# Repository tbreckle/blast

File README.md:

<div align="center">

### Button Logic & Arcade Simulation Terminal

**An open-source arcade control panel: 16 buttons, 11 dimmable LEDs, an OLED menu, and a desktop app to configure all of it.**

[**Download**](https://github.com/tbreckle/blast/releases) ·
[Features](#-features) ·
[Quick start](#-quick-start) ·
[BLAST protocol](#-light-it-up-from-your-games) ·
[Building](#-building-from-source) ·
[Contributing](#-contributing)

</div>

---

## 🕹️ What is this?

B.L.A.S.T. is the button box that sits next to your lightgun or arcade cabinet. It presents itself to the PC as a plain **USB keyboard**, so every game and emulator understands it without drivers. Each game gets its own **profile** of key bindings, which you pick on the built-in **OLED** or let your frontend switch automatically. The **button LEDs** can be driven live by the game (blink the coin button, breathe the start button, flash on a hit) over a simple text protocol.

It's a full stack in one repo:

| | Component | Stack |
|---|---|---|
| 🧠 | [**Firmware**](firmware/) | C++ / Arduino on a Raspberry Pi Pico (RP2040 / RP2350) |
| 🖥️ | [**Config app**](app/) | Rust + [Slint](https://slint.dev), native on Linux, Windows and macOS |
| 🔌 | [**PCB**](pcb/) | KiCad schematic, layout and production files |

## ✨ Features

<table>
<tr>
<td width="50%" valign="top">

#### 🎮 Controller
- **16 inputs**: Start, Coin, Action A and Action B for two players, Pause / Save / Load, and a 5-way navigation pad
- **Plug and play**: USB HID keyboard, no drivers needed
- **Key combos**: letters, digits, Space, Enter, F1–F24, with Ctrl / Alt / Shift
- **Interrupt-driven debouncing** with a polling fallback

</td>
<td width="50%" valign="top">

#### 💡 Lighting
- **11 LED buttons** on a 12-channel TLC59711 PWM driver with gamma correction
- **Modes**: off, on, blink, breathe and flash sequences
- **Game-driven**: games and tools set the LEDs live over the [BLAST protocol](firmware/BLAST_PROTOCOL.md)
- **RGB status LED** that shows boot, config and run state

</td>
</tr>
<tr>
<td width="50%" valign="top">

#### 📟 On-device
- **128×64 OLED** menu to browse and pick profiles
- **Up to 50 profiles** stored in flash
- **Automatic profile switching** by game name, for example from MAMEHooker
- **Service menu** for the service and test buttons

</td>
<td width="50%" valign="top">

#### 🖥️ Config app
- **Create, edit and delete profiles** and press a key to bind it
- **Sync status** that shows what's changed and what's saved on the device
- **Version check**: warns when app and firmware don't match
- **Light / Dark / System** themes

</td>
</tr>
</table>

## 🚀 Quick start

1. **Grab the latest release** from the [Releases page](https://github.com/tbreckle/blast/releases):

   | File | What it is |
   |---|---|
   | `blast-firmware-X.Y.Z.uf2` | Firmware for the controller |
   | `blast-app-X.Y.Z-linux-x86_64.tar.gz` | Config app for Linux |
   | `blast-app-X.Y.Z-windows-x86_64.zip` | Config app for Windows |
   | `blast-app-X.Y.Z-macos-universal.tar.gz` | Config app for macOS (Apple Silicon + Intel) |

2. **Flash the firmware**: hold **BOOTSEL** while plugging in the Pico and drop the `.uf2` onto the `RPI-RP2` drive that shows up.
3. **Run the app**, pick the **B.L.A.S.T.** port (it's preselected), and create your first profile.
4. **Play.** Choose the profile on the OLED, or let your frontend switch to it.

> [!TIP]
> Use the app and firmware from the **same release**. The app shows a warning in the status bar when they differ. Builds labeled `0.0.0+<commit>` are unofficial development builds.

## 🌈 Light it up from your games

Out of the box the serial port speaks the **BLAST protocol**: one line of plain ASCII per command, with no handshake and no replies. Anything that can write to a serial port can drive the LEDs.

```bash
stty -F /dev/ttyACM0 115200 raw -echo
printf 'B1\n'          > /dev/ttyACM0   # host started: all LEDs off
printf 'BLxtcrisis\n'  > /dev/ttyACM0   # load the profile for "tcrisis"
printf 'B4x0x2x200\n'  > /dev/ttyACM0   # both coin buttons blink fast
printf 'B3x1x4x1500\n' > /dev/ttyACM0   # P1 start breathes with a 3 s cycle
printf 'B5x2x3x5\n'    > /dev/ttyACM0   # P2 action A flashes 5 times
```

The full spec is in [`firmware/BLAST_PROTOCOL.md`](firmware/BLAST_PROTOCOL.md).

## 🧩 How it fits together

```mermaid
flowchart LR
    subgraph PC["🖥️ PC"]
        game["Game / emulator"]
        hook["LED output tool<br/>(e.g. MAMEHooker)"]
        app["B.L.A.S.T. config app"]
    end

    subgraph Pico["🧠 RP2040 / RP2350"]
        fw["Firmware"]
    end

    fw -- "USB HID keystrokes" --> game
    hook -- "BLAST text protocol<br/>(USB serial)" --> fw
    app <-- "SLIP binary protocol<br/>(same USB serial)" --> fw

    fw --- mcp["MCP23017<br/>16 buttons"]
    fw --- tlc["TLC59711<br/>12 LED channels"]
    fw --- oled["SSD1306<br/>128×64 OLED"]
```

One USB cable carries both the keyboard and the serial port. The serial port runs one of two protocols at a time: the **BLAST** text protocol for games (the default), or the binary **SLIP** protocol that the config app switches to while it's connected. The OLED shows which one is active (`B` or `S`).

<details>
<summary><b>🔩 Hardware bill of materials</b></summary>

| Part | Role | Interface |
|---|---|---|
| Raspberry Pi Pico (W) / RP2350 | Main MCU | – |
| MCP23017 | 16 button inputs, active-low with pull-ups | I²C `0x20` + interrupt |
| TLC59711 | 12-channel 16-bit PWM LED driver | Bit-banged SPI (GP6 / GP7) |
| SSD1306 | 128×64 OLED | I²C `0x3C` |
| RGB LED | Status indicator | GPIO |

KiCad sources and fabrication outputs (BOM, positions, netlist) are in [`pcb/blast/`](pcb/blast/).

</details>

<details>
<summary><b>🗂️ Repository layout</b></summary>

```
blast/
├── firmware/              # Arduino/C++ firmware for RP2040/RP2350
│   ├── firmware.ino       # Entry point, pin map, button + LED handling
│   ├── blast_protocol.*   # BLAST text protocol (host LED control)
│   ├── serializer.*       # SLIP binary protocol (config app)
│   ├── menu.*             # OLED menu state machine
│   ├── debounce_mcp.*     # MCP23017 debouncing
│   ├── storage.*          # Profile persistence and migrations
│   └── flash.sh           # One-shot flashing via picotool
├── app/                   # Rust/Slint configuration tool
│   ├── ui/app.slint       # UI definition
│   └── src/               # ui.rs, protocol.rs, slip.rs, types.rs, keymap.rs
├── pcb/blast/             # KiCad project + production files
├── scripts/               # version.sh, changelog.sh, test.sh
└── .github/workflows/     # CI, release-start, release-finish
```

</details>

## 🔧 Building from source

<details>
<summary><b>🖥️ Config app (Rust)</b></summary>

**Requirements:** Rust 1.92+ (needed by Slint 1.18). On Linux you also need `libudev-dev`, `libfontconfig-dev` and `pkg-config`.

```bash
cd app
cargo run --release     # build and launch
cargo test              # unit tests
cargo clippy            # lint (warnings fail CI)
cargo fmt --check       # formatting check
```

</details>

<details>
<summary><b>🧠 Firmware (Arduino-Pico)</b></summary>

**Requirements:**
- [Arduino-Pico](https://github.com/earlephilhower/arduino-pico) core by Earle F. Philhower, III, **version 6.1.1**<br/>
  Boards Manager URL: `https://github.com/earlephilhower/arduino-pico/releases/download/global/package_rp2040_index.json`
- Libraries:

  | Library | Version |
  |---|---|
  | Adafruit MCP23017 Arduino Library | 2.3.2 |
  | Adafruit SSD1306 | 2.5.16 |
  | Adafruit GFX Library | 1.12.4 |
  | Adafruit BusIO | 1.17.4 |

  Wire, SPI, EEPROM, Keyboard, HID_Keyboard and tusb-hid ship with the Arduino-Pico core.

**With `arduino-cli`** (from the repo root, same as CI):

```bash
arduino-cli compile \
  --fqbn "$(jq -r '.board + ":" + .configuration' .vscode/arduino.json)" \
  --output-dir _build firmware/firmware.ino

cd firmware && ./flash.sh        # finds the controller by VID/PID, reboots it into the bootloader, flashes it
```

> [!IMPORTANT]
> Always build with the full FQBN from `.vscode/arduino.json`. It selects the Pico W boot stage and the 128 KB filesystem layout. With another flash layout the stored profiles are lost.

**With the Arduino IDE:** open `firmware/firmware.ino`, select the Raspberry Pi Pico W board (Arduino-Pico core) with a 128 KB filesystem and the Pico SDK USB stack, then upload.

</details>

## 🤝 Contributing

Contributions are welcome! The project uses **GitFlow**: branch `feature/*` off `develop` and open a PR back to `develop`. CI builds the app on all three platforms, builds the firmware and runs the linters on every push.

- 📖 [GITFLOW.md](GITFLOW.md): branching, versioning and releases
- ⚙️ [.github/WORKFLOWS.md](.github/WORKFLOWS.md): the CI/CD pipelines
- 📝 [CHANGELOG.md](CHANGELOG.md): add your change under `## [Unreleased]`

## 📜 License

B.L.A.S.T. is released under the [MIT License](LICENSE).

### Made with Slint

<a href="https://slint.dev">
  <picture>
    <source media="(prefers-color-scheme: dark)" srcset="https://slint.dev/logo/MadeWithSlint-logo-dark.svg">
    
  </picture>
</a>

The configuration tool's user interface is built with [Slint](https://slint.dev), used under the [Slint Royalty-free Desktop, Mobile, and Web Applications License 2.0](https://github.com/slint-ui/slint/blob/master/LICENSES/LicenseRef-Slint-Royalty-free-2.0.md). The app also shows the Slint attribution under **Help → About B.L.A.S.T.**

---

<div align="center">

**🪙 INSERT COIN TO CONTINUE 🪙**

<sub>Made with 🔥 for light gun fans.</sub>

</div>

---

## ⚖️ Legal Disclaimer

**USE AT YOUR OWN RISK**

This software and firmware are provided "AS IS" without warranty of any kind, express or implied, including but not limited to the warranties of merchantability, fitness for a particular purpose, and non-infringement.

**Important Notes:**

- The developers and contributors of this project assume **no liability** for any damages, losses, or issues arising from the use, misuse, or inability to use this software or hardware
- This includes, but is not limited to: hardware damage, data loss, system malfunction, or any other direct or indirect consequences
- By using this software, you acknowledge that you do so at your own risk
- Users are responsible for ensuring compatibility with their systems and compliance with local regulations
- This project is an independent effort and is not affiliated with or endorsed by any hardware manufacturer unless explicitly stated

**For Hobbyist and Educational Use:**

This project is intended for personal, educational, and hobbyist use. Users modifying firmware or hardware configurations should have appropriate technical knowledge and accept full responsibility for their modifications.

If you're unsure about any aspect of installation or use, please consult the documentation or seek assistance from knowledgeable individuals before proceeding.

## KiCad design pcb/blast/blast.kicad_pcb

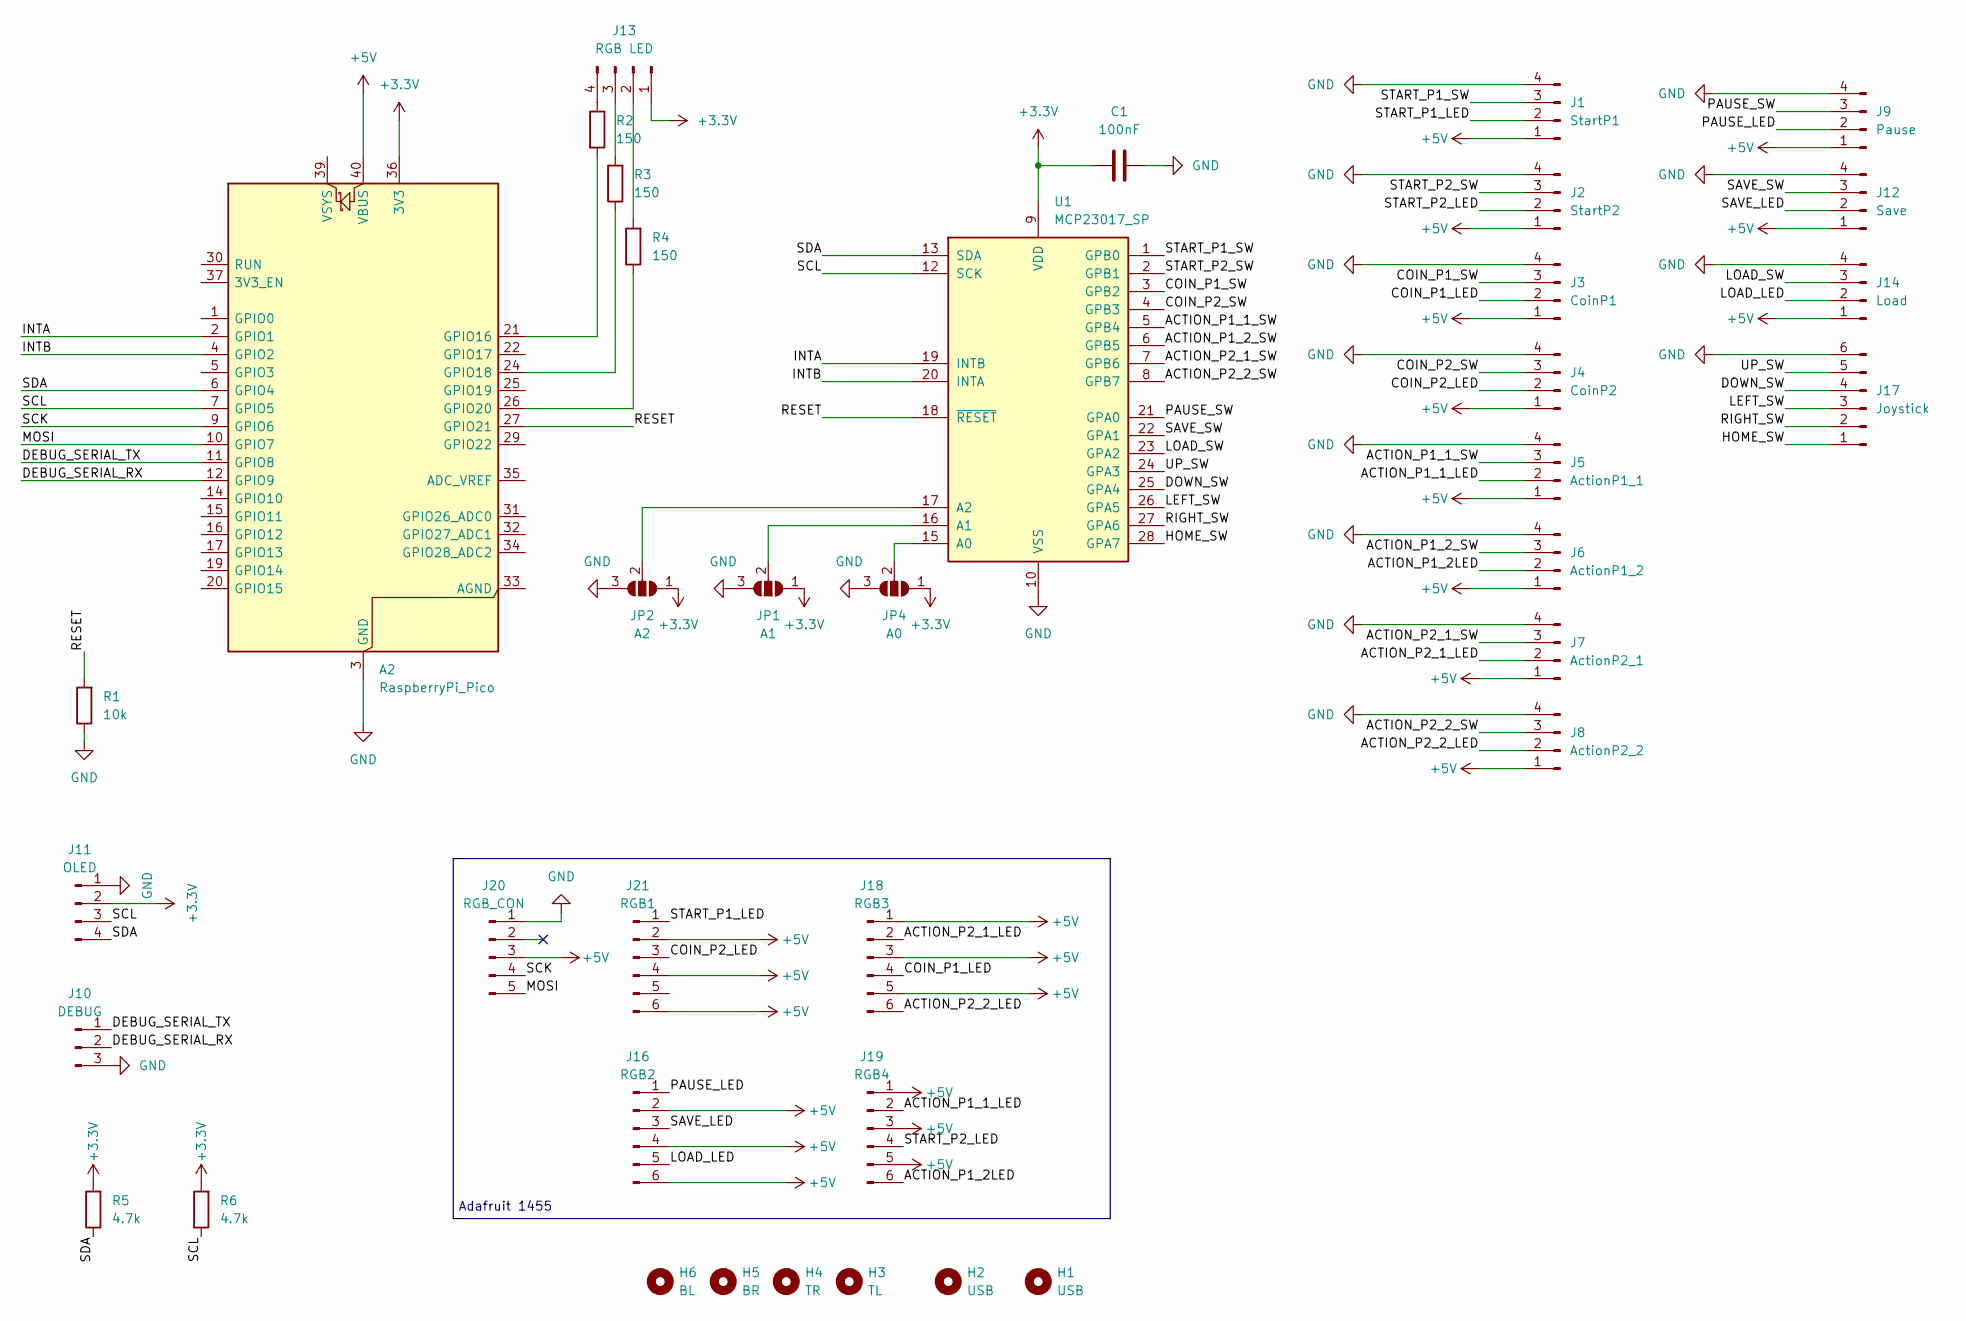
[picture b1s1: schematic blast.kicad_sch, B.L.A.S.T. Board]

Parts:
A2: RaspberryPi_Pico; RaspberryPi_Pico_Common_Unspecified
C1: 100nF; C_1206_3216Metric_Pad1.33x1.80mm_HandSolder
H1, H2: USB; MountingHole_4.3mm_M4
H3: TL; MountingHole_3.2mm_M3
H4: TR; MountingHole_3.2mm_M3
H5: BR; MountingHole_3.2mm_M3
H6: BL; MountingHole_3.2mm_M3
J1: StartP1; JST_XH_B4B-XH-A_1x04_P2.50mm_Vertical
J2: StartP2; JST_XH_B4B-XH-A_1x04_P2.50mm_Vertical
J3: CoinP1; JST_XH_B4B-XH-A_1x04_P2.50mm_Vertical
J4: CoinP2; JST_XH_B4B-XH-A_1x04_P2.50mm_Vertical
J5: ActionP1_1; JST_XH_B4B-XH-A_1x04_P2.50mm_Vertical
J6: ActionP1_2; JST_XH_B4B-XH-A_1x04_P2.50mm_Vertical
J7: ActionP2_1; JST_XH_B4B-XH-A_1x04_P2.50mm_Vertical
J8: ActionP2_2; JST_XH_B4B-XH-A_1x04_P2.50mm_Vertical
J9: Pause; JST_XH_B4B-XH-A_1x04_P2.50mm_Vertical
J10: DEBUG; PinSocket_1x03_P2.54mm_Vertical
J11: OLED; JST_XH_B4B-XH-A_1x04_P2.50mm_Vertical
J12: Save; JST_XH_B4B-XH-A_1x04_P2.50mm_Vertical
J13: RGB LED; JST_XH_B4B-XH-A_1x04_P2.50mm_Vertical
J14: Load; JST_XH_B4B-XH-A_1x04_P2.50mm_Vertical
J16: RGB2; PinSocket_2x03_P2.54mm_Vertical
J17: Joystick; JST_XH_B6B-XH-A_1x06_P2.50mm_Vertical
J18: RGB3; PinSocket_2x03_P2.54mm_Vertical
J19: RGB4; PinSocket_2x03_P2.54mm_Vertical
J20: RGB_CON; PinSocket_1x05_P2.54mm_Vertical
J21: RGB1; PinSocket_2x03_P2.54mm_Vertical
JP1: A1; SolderJumper-3_P1.3mm_Open_RoundedPad1.0x1.5mm_NumberLabels
JP2: A2; SolderJumper-3_P1.3mm_Open_RoundedPad1.0x1.5mm_NumberLabels
JP4: A0; SolderJumper-3_P1.3mm_Open_RoundedPad1.0x1.5mm_NumberLabels
R1: 10k; R_1206_3216Metric_Pad1.30x1.75mm_HandSolder
R2, R3, R4: 150; R_1206_3216Metric_Pad1.30x1.75mm_HandSolder
R5, R6: 4.7k; R_1206_3216Metric_Pad1.30x1.75mm_HandSolder
U1: MCP23017_SP; DIP-28_W7.62mm

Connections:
+3.3V: A2.36 (3V3), C1.1, J11.2, J13.1, JP1.1 (A), JP2.1 (A), JP4.1 (A), R5.2, R6.2, U1.9 (VDD)
+5V: A2.40 (VBUS), J1.1, J2.1, J3.1, J4.1, J5.1, J6.1, J7.1, J8.1, J9.1, J12.1, J14.1, J16.2, J16.4, J16.6, J18.1, J18.3, J18.5, J19.1, J19.3, J19.5, J20.3, J21.2, J21.4, J21.6
/ACTION_P1_1_LED: J5.2, J19.2
/ACTION_P1_1_SW: J5.3, U1.5 (GPB4)
/ACTION_P1_2LED: J6.2, J19.6
/ACTION_P1_2_SW: J6.3, U1.6 (GPB5)
/ACTION_P2_1_LED: J7.2, J18.2
/ACTION_P2_1_SW: J7.3, U1.7 (GPB6)
/ACTION_P2_2_LED: J8.2, J18.6
/ACTION_P2_2_SW: J8.3, U1.8 (GPB7)
/COIN_P1_LED: J3.2, J18.4
/COIN_P1_SW: J3.3, U1.3 (GPB2)
/COIN_P2_LED: J4.2, J21.3
/COIN_P2_SW: J4.3, U1.4 (GPB3)
/DEBUG_SERIAL_RX: A2.12 (GPIO9), J10.2
/DEBUG_SERIAL_TX: A2.11 (GPIO8), J10.1
/DOWN_SW: J17.4, U1.25 (GPA4)
/HOME_SW: J17.1, U1.28 (GPA7)
/INTA: A2.2 (GPIO1), U1.19 (INTB)
/INTB: A2.4 (GPIO2), U1.20 (INTA)
/LEFT_SW: J17.3, U1.26 (GPA5)
/LOAD_LED: J14.2, J16.5
/LOAD_SW: J14.3, U1.23 (GPA2)
/MOSI: A2.10 (GPIO7), J20.5
/PAUSE_LED: J9.2, J16.1
/PAUSE_SW: J9.3, U1.21 (GPA0)
/RESET: A2.27 (GPIO21), R1.2, U1.18 (~RESET)
/RIGHT_SW: J17.2, U1.27 (GPA6)
/SAVE_LED: J12.2, J16.3
/SAVE_SW: J12.3, U1.22 (GPA1)
/SCK: A2.9 (GPIO6), J20.4
/SCL: A2.7 (GPIO5), J11.3, R6.1, U1.12 (SCK)
/SDA: A2.6 (GPIO4), J11.4, R5.1, U1.13 (SDA)
/START_P1_LED: J1.2, J21.1
/START_P1_SW: J1.3, U1.1 (GPB0)
/START_P2_LED: J2.2, J19.4
/START_P2_SW: J2.3, U1.2 (GPB1)
/UP_SW: J17.5, U1.24 (GPA3)
GND: A2.3 (GND), A2.8 (GND), A2.13 (GND), A2.18 (GND), A2.23 (GND), A2.28 (GND), A2.38 (GND), C1.2, J1.4, J2.4, J3.4, J4.4, J5.4, J6.4, J7.4, J8.4, J9.4, J10.3, J11.1, J12.4, J14.4, J17.6, J20.1, JP1.3 (B), JP2.3 (B), JP4.3 (B), R1.1, U1.10 (VSS)
unnamed: A2.21 (GPIO16), R2.2
unnamed: A2.24 (GPIO18), R3.1
unnamed: A2.26 (GPIO20), R4.1
unnamed: J13.2, R4.2
unnamed: J13.3, R3.2
unnamed: J13.4, R2.1
unnamed: JP1.2 (C), U1.16 (A1)
unnamed: JP2.2 (C), U1.17 (A2)
unnamed: JP4.2 (C), U1.15 (A0)

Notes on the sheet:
Adafruit 1455

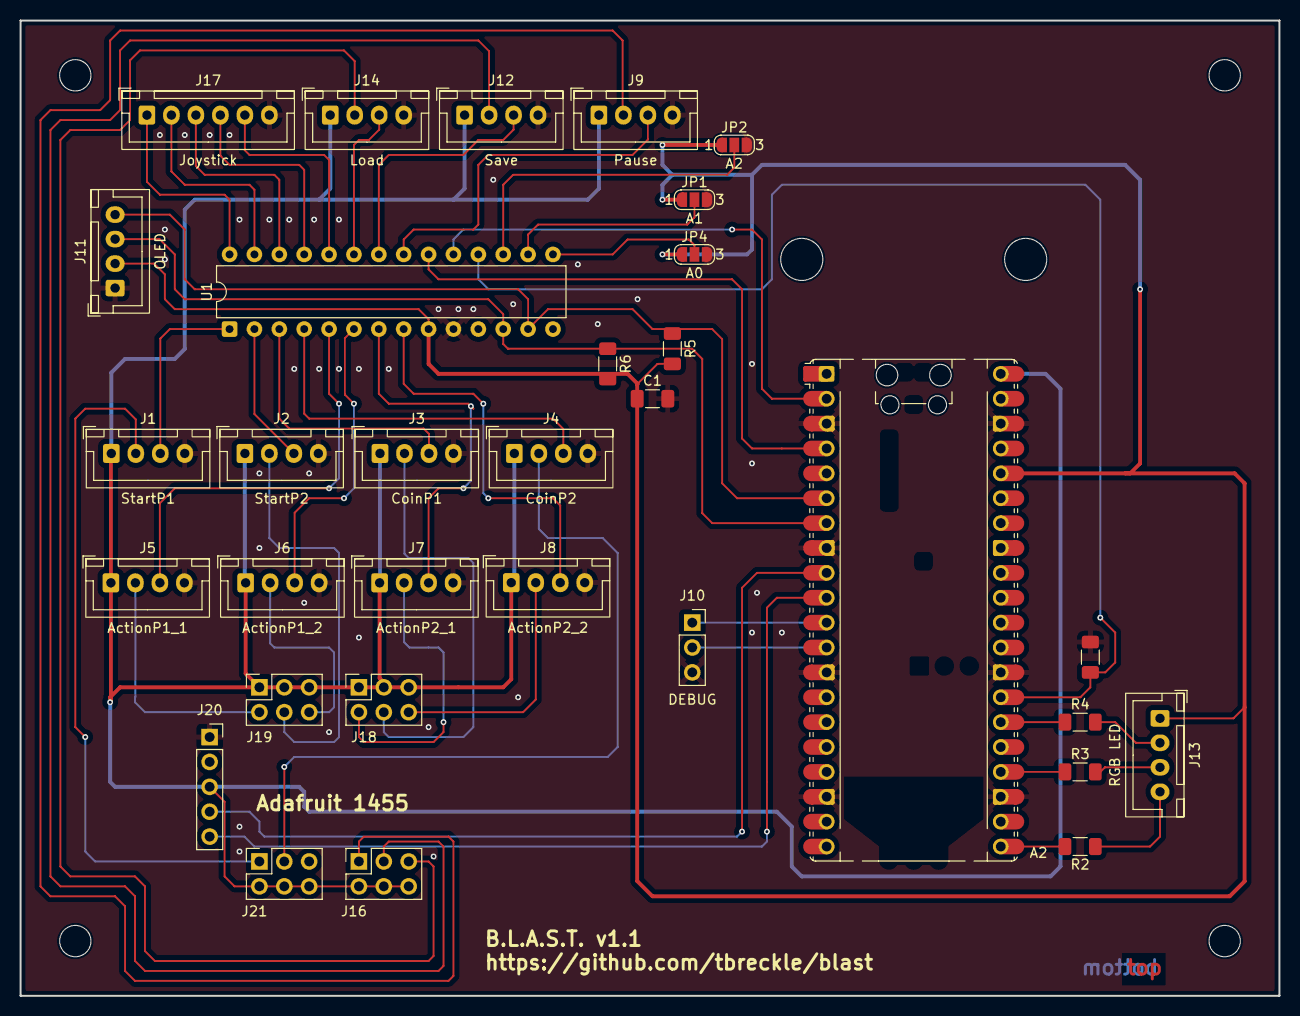
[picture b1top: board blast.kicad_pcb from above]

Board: 2 copper layers, 128.5 x 99.6 mm, 38 parts (0 on the bottom side), 48 nets.

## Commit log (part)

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2026-02-01 Initial
2026-02-01 Added license
2026-02-07 Initialize and properly run all hardware. Some bugfixes.
2026-03-26 Fix keypress missing bug, fix service menu display.
2026-03-26 Adds claude code files, adds overlay with spinner on long app operations.
2026-03-27 Fix some bugs on Windows with the app.
2026-03-31 Fix buttonpresses detection and support holding buttons.

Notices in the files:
README.md:
License: MIT
